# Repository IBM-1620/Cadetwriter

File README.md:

# Cadetwriter
Developed as a by-product of the IBM 1620 Jr. project, the Cadetwriter is a general-purpose ASCII terminal.  It can be connected via RS-232 or USB to any mini, micro, mainframe, or replica computer as a terminal device.  A commercial quality IBM/Lexmark Wheelwriter 1000 was adapted by interposing a circuit board containing a Teensy 3.5 microcontroller between the typewriter's keyboard and motherboard.  Custom firmware controls the typewriter and communicates with the host computer.  To support the full ASCII character set, characters not on the printwheel are synthesized using overprinted characters and "period graphics".  The Cadetwriter can print up to 16cps and is a reliable, low-maintenance, low-cost substitute for Teletype, DECwriter, Diablo, Spinwriter, Imagewriter, etc. teleprinters.

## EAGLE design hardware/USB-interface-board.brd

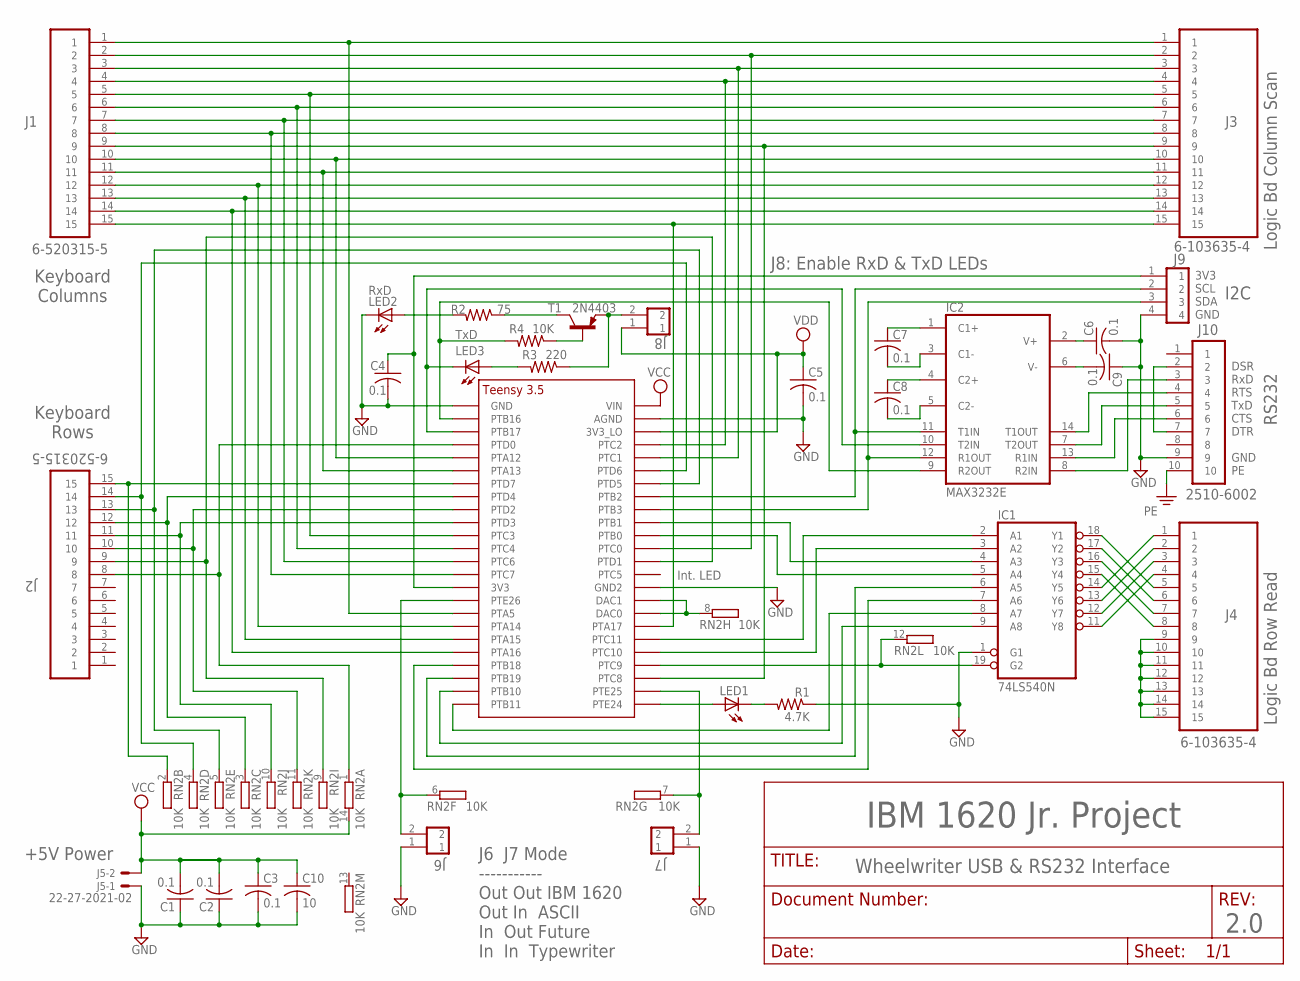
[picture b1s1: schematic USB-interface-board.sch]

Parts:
C1, C2, C3, C4, C5, C6, C7, C8, C9: 0.1; C025-025X050
C10: 10; C050-035X075
IC1: 74LS540N; DIL20
IC2: MAX3232E; DIL16
J1: 6-520315-5
J2: 6-520315-5; 6-520315-5-U
J3, J4: 6-103635-4
J5: 22-27-2021-02; 6410-02
J6, J7, J8: HEADER-1X2
J9: HEADER-1X4
J10: 2510-6002; PAK100/2500-10
LED1: LED3MM
LED2: RxD; LED3MM
LED3: TxD; LED3MM
R1: 4.7K; 0204/5
R2: 75; 0204/5
R3: 220; 0204/5
R4: 10K; 0204/5
RN2: 10K; DIL14
T1: 2N4403; TO92
U$1: TEENSY_3.5_BASIC

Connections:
GND: C1.1, C2.1, C3.2, C4.2, C5.2, C6.2, C9.1, C10.2, IC1.1 (G1), IC1.10 (GND), IC2.15 (GND), J5.1, J6.1, J7.1, J9.4, J10.9, LED2.K (C), R1.1, U$1.AGND, U$1.GND, U$1.GND2
unnamed: J1.2, J3.2, U$1.PTC0
unnamed: J1.3, J3.3, U$1.PTC1
unnamed: J1.4, J3.4, U$1.PTC2
unnamed: J1.5, J3.5, U$1.PTC3
unnamed: J1.6, J3.6, U$1.PTC4
unnamed: J1.7, J3.7, U$1.PTC6
unnamed: J1.8, J3.8, U$1.PTC7
unnamed: J1.9, J3.9, U$1.PTC8
unnamed: J1.10, J3.10, U$1.PTA12
unnamed: J1.11, J3.11, U$1.PTA13
unnamed: J1.12, J3.12, U$1.PTA14
unnamed: J1.13, J3.13, U$1.PTA15
unnamed: J1.14, J3.14, U$1.PTA16
unnamed: J1.15, J3.15, U$1.PTA17
unnamed: J2.15, RN2.2 (1), U$1.PTD7
unnamed: J2.14, RN2.4 (1), U$1.PTD6
unnamed: J2.13, RN2.5 (1), U$1.PTD5
unnamed: J2.12, RN2.3 (1), U$1.PTD4
unnamed: J2.11, RN2.10 (1), U$1.PTD3
unnamed: J2.10, RN2.11 (1), U$1.PTD2
unnamed: J2.9, RN2.9 (1), U$1.PTD1
unnamed: J2.8, RN2.1, U$1.PTD0
unnamed: IC1.11 (Y8), J4.4
unnamed: IC1.12 (Y7), J4.3
unnamed: IC1.13 (Y6), J4.2
unnamed: IC1.14 (Y5), J4.1
unnamed: IC1.15 (Y4), J4.8
unnamed: IC1.16 (Y3), J4.7
unnamed: IC1.17 (Y2), J4.6
unnamed: IC1.18 (Y1), J4.5
unnamed: J4.9, J4.10, J4.11, J4.12, J4.13, J4.14, J4.15
unnamed: IC1.8 (A7), U$1.PTB11
unnamed: IC1.9 (A8), U$1.PTB10
unnamed: IC1.6 (A5), U$1.PTB19
unnamed: IC1.7 (A6), U$1.PTB18
unnamed: IC1.5 (A4), U$1.PTB0
unnamed: IC1.4 (A3), U$1.PTB1
unnamed: IC1.2 (A1), U$1.PTC11
unnamed: IC1.3 (A2), U$1.PTC10
unnamed: J6.2, RN2.6 (1), U$1.PTE26
unnamed: C6.1, IC2.2 (V+)
unnamed: LED1.K (C), R1.2
unnamed: LED1.A, U$1.PTE24
unnamed: J7.2, RN2.7 (1), U$1.PTE25
unnamed: C9.2, IC2.6 (V-)
unnamed: IC2.14 (T1OUT), J10.4
unnamed: C4.1, J9.1, U$1.3V3
unnamed: IC2.12 (R1OUT), J9.3, U$1.PTB3
unnamed: C7.1, IC2.1 (C1+)
unnamed: J10.2, J10.7
unnamed: IC1.19 (G2), RN2.12 (1), U$1.PTC9
unnamed: J1.1, J3.1, U$1.PTA5
unnamed: C7.2, IC2.3 (C1-)
unnamed: C8.1, IC2.4 (C2+)
unnamed: C8.2, IC2.5 (C2-)
unnamed: IC2.11 (T1IN), J9.2, U$1.PTB2
unnamed: IC2.9 (R2OUT), R4.2, U$1.PTB16
unnamed: IC2.10 (T2IN), LED3.K (C), U$1.PTB17
unnamed: IC2.7 (T2OUT), J10.5
unnamed: IC2.8 (R2IN), J10.3
unnamed: IC2.13 (R1IN), J10.6
unnamed: R2.1, T1.1 (C)
unnamed: LED3.A, R3.2
unnamed: LED2.A, R2.2
unnamed: RN2.8 (1), U$1.DAC0, U$1.DAC1
unnamed: J8.2, R3.1, T1.3 (E)
unnamed: R4.1, T1.2 (B)
PE: J10.10
VCC: C1.2, C2.2, C3.1, C10.1, IC1.20 (VCC), J5.2, RN2.14 (2), U$1.VIN
VDD: C5.1, IC2.16 (VDD), J8.1, U$1.3V3_LO

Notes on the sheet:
2.0
IBM 1620 Jr. Project
Int. LED
Wheelwriter USB & RS232 Interface
J8: Enable RxD & TxD LEDs
J6 J7 Mode ----------- Out Out IBM 1620 Out In ASCII In Out Future In In Typewriter
Keyboard Columns
Keyboard Rows
Logic Bd Column Scan
Logic Bd Row Read
3V3 SCL SDA GND
I2C
+5V Power
DSR RxD RTS TxD CTS DTR GND PE
RS232

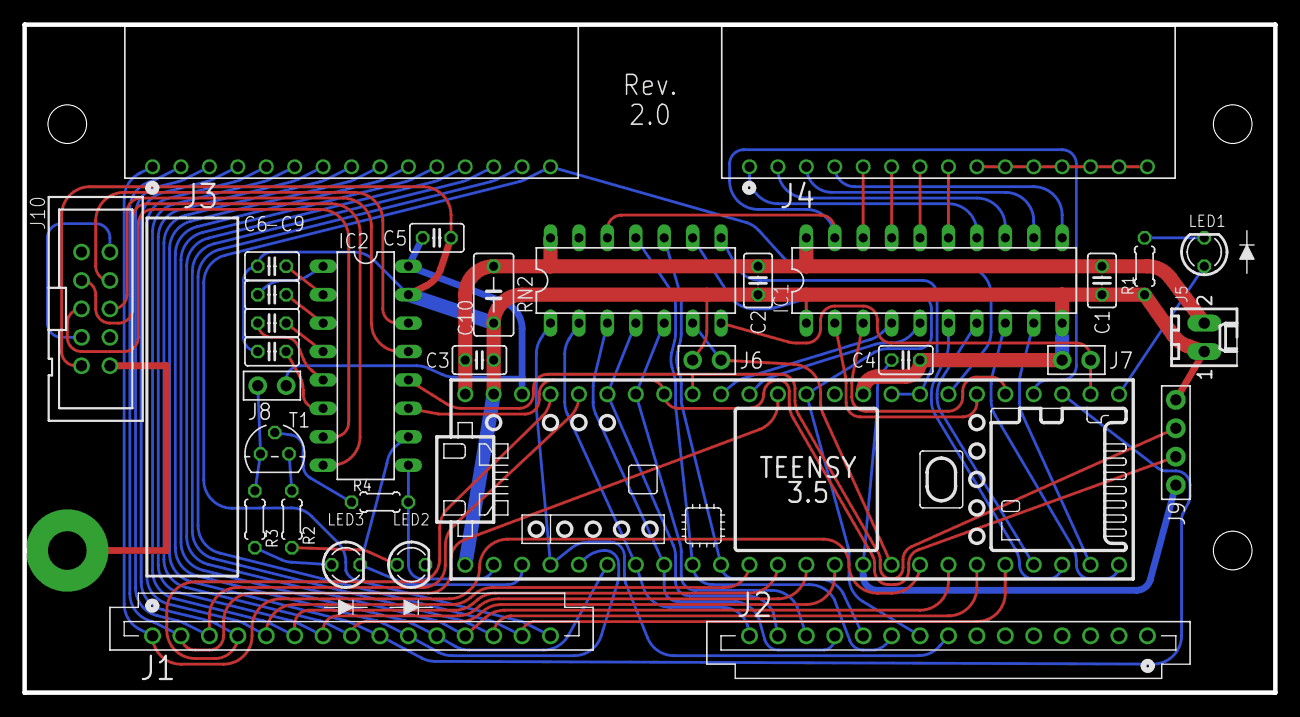
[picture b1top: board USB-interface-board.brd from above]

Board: 2 copper layers, 111.8 x 59.7 mm, 35 parts (0 on the bottom side), 70 nets.

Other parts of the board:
U$2, U$4, U$5: MOUNTING_HOLE

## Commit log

2019-07-28 Add Rev. 2.0 version of CAD diagram
2019-07-28 Enlarge scale of CAD diagram to fill the page
2019-08-02 Initial release of adaptation instructions for Rev 2.0
2019-08-02 Add files via upload
    Firmware release 5R4beta3 binary code.
2019-08-12 Update available baud rate due to limitation of Teensy 3.5.
2019-08-12 Initial flyer used at VCF West 2019.
2019-08-12 Update with changes from VCF West 2019.
2019-08-13 Cleaned up printed ASCII character set.
2019-08-13 Correct part number for 4.7K resistor
2019-08-29 GPL v3.0
    This program is free software: you can redistribute it and/or modify it under the terms of the GNU General Public License as published by the Free Software Foundation, either version 3 of the License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
    This program is distributed in the hope that it will be useful, but WITHOUT ANY WARRANTY; without even the implied warranty of MERCHANTABILITY or FITNESS FOR A PARTICULAR PURPOSE. See the GNU General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
2019-08-31 Source code for Cadetwriter firmware.
2019-08-31 Cadetwriter firmware version 5R4 compiled code.
2019-08-31 Updated flyer with firmware v.5R4 character set.
2019-09-02 Replace PNG diagrams with SVG and add appendix for latching connectors
    1. The schematic diagram and the CAD diagram are updated now to use
    SVG graphics rather than PNG raster images. This allows full
    resolution when zooming in on those diagrams in the PDF rendering of
    the document.
    2. Rather than referring to the earlier adaptation instructions for
    the Rev. 1.6 board, now the alternate instruction for using FFC cables
2019-09-02 Add EAGLE CAD files for USB & RS232 Interface Board
2019-09-02 Add gerber files for USB & RS232 Interface Board
2019-10-29 Add files via upload
    Update flyer with reference to Slack discussion forums and new CHM logo.
2019-11-10 Version 5R5 includes these changes: Added support for semi-automatic paper loading. Increased time for ISR delay to deal with overlapping column scans. Adjusted timing of unshifted, shifted, and code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
2019-11-12 Deleted older flyers.
2019-11-12 Latest Cadetwriter flyer.
2019-11-12 Latest version of keyboard matrix.
2019-11-13 Upload VCF West 2019 Cadetwriter presentation.
2019-11-13 Upload VCF West 2019 presentation.
2019-11-14 Version 5R6 is a minor revision with the set of available baud rates corrected.
2019-11-19 Update price and contact information for Wavelink FFC cables. Remove extra blank page at the end.
2019-12-05 Use SlowSoftSerial to get lower baud rates
    For setup and user interface purposes, the serial interfaces
    are still USB and RS232. If the user chooses RS232, all the
    lower baud rates in the list are now available. If one of the
    lower baud rates is selected, then at the end of setup the
    serial mode is changed to RS232_SLOW and the SlowSoftSerial
    library object is used instead of the Serial1 hardware UART.
2019-12-05 Add missed baud rates to configuration parser
2019-12-29 Removed some unneeded timing dependencies.
2020-01-20 Restore handling of Enter to accept old baud rate in settings
    Also removed an unneeded while loop. The function of the while
    loop had already been extracted into a helper function.
2020-01-21 Fix handling of serial mode setting in EEPROM (refactored)
    Before I had added a third value to `serial` to encode the use of
    SlowSoftSerial, but that value couldn't be stored in EEPROM without
    breaking backward compatibility and diverging from the semantics in
    the UI, so it required some messy fiddling around when reading or
    writing EEPROM. Messy enough that I didn't get it right the first
    time. Now I have restored the original meaning of `serial` and added
2020-02-12 Update parts list
    1. Substitute an ROHS variant part for the 2x5 header, 4-wall, keyed
    that is about to be end-of-life.
    2. Revise the FFC cable sources to remove the 80-conductor cable
    alternative since Wavelink has made a production run of the proper
    15-conductor cables.
2020-03-19 Adopted the SlowSoftSerial library to allow slow baud rates. [Thanks to Paul Williamson.] Fixed corner cases of margin and tab settings. Added a beep when an invalid character is typed in setup mode.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
2020-03-22 Expanded the set of invalid setup characters that trigger a beep. Improved global counter synchronization comments.
2020-03-30 Renamed Operation Guide to User Guide.
2020-05-13 Added Wheelwriter 1500 to keyboard_matrix.xls. [Thanks to Chris Coley.] Added wheelwriter_1500_user_manual.pdf. [ " ]
2020-05-14 Added Wheelwriter 30 Series II User Manual.
2020-05-15 Added more Wheelwriter User Manuals.
2020-05-16 Added print sample for each machine.
2020-05-23 Updated keyboard matrix spreadsheet with Wheelwriter 1500. Added ISO/IEC escape sequence documentation. Added Paul Williamson's 3D-printable paper guide.
2020-10-23 Replaced end-of-lifed Molex pins with newer substitute.
2020-11-29 Serial_Interface_Board.ino revision 5R10. - Corrected RS-232 hardware flow control. - Fixed a problem with software flow control. - Switched sense of flow_in_on and flow_out_on to be more consistent.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
2020-11-30 Updated file access mode.
2021-02-17 Added ASCII printwheel character set and printwheel character ordering.
2021-02-20 Correct typo.
2021-02-27 Added more printwheel information.
2021-03-14 Updated IBM 1620 Max keyboard layout.
2021-03-14 Corrected printwheel data.
2021-03-15 Added Operations page.
2021-03-18 Corrected mapping of margin and tab control keys.
2021-04-26 Major update to firmware (version 6R0) with these changes: Developed new Spin-Hit-Move (SHM) printer timing model. Added developer column scan timing measurements and rewrote printer timing. Added co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
    Public release of the Cadetwriter User Guide.
2021-04-28 Updated Cadetwriter User Guide based on feedback from Paul Williamson.
2021-07-29 Found more Wheelwriter manuals.
2021-07-29 Corrected file permissions.
2021-07-30 Added more motherboard numbers.
2021-10-26 Corrected typo in Wavelink part number 254-015-0155-AB in Parts List and Appendix; updated costs in Parts List.
2022-04-16 Add PDF version of the schematic to allow viewing without opening in the EAGLE CAD app.
